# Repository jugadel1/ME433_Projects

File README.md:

# ME433

## HW2 - Alternate LED blinks using PIC32MX170F256B

- initializes A4 as input, and B4 and B5 as output
- in the infinite loop, wait until a newline is received from the computer, print it back, and if the USER button is not pressed, blink the LEDs 5 times over 2.5 seconds
- Edit the code to receive two numbers from the user over the serial port, the number of times to blink and how long each blink period should be.

## HW3 - Plot to terminal using UART using PIC32MX170F256B

- Every time you push the USER button, sends a single cycle of a sine wave in 100 data points to UART, with a 0.01 second delay between each data point.

- Uses sin_plotter.py to view the data as a graph.

## HW6 - Communicate with GPIO port extender using I2C

- The goal is to read from the button connected to GP0, and if pushed, turns on an LED connected to GP7, else turns off LED

## HW 14 - RC Motor Control

- Use the PIC to sweep the angle of the RC servo from 45 degrees to 135 degrees every 4 seconds

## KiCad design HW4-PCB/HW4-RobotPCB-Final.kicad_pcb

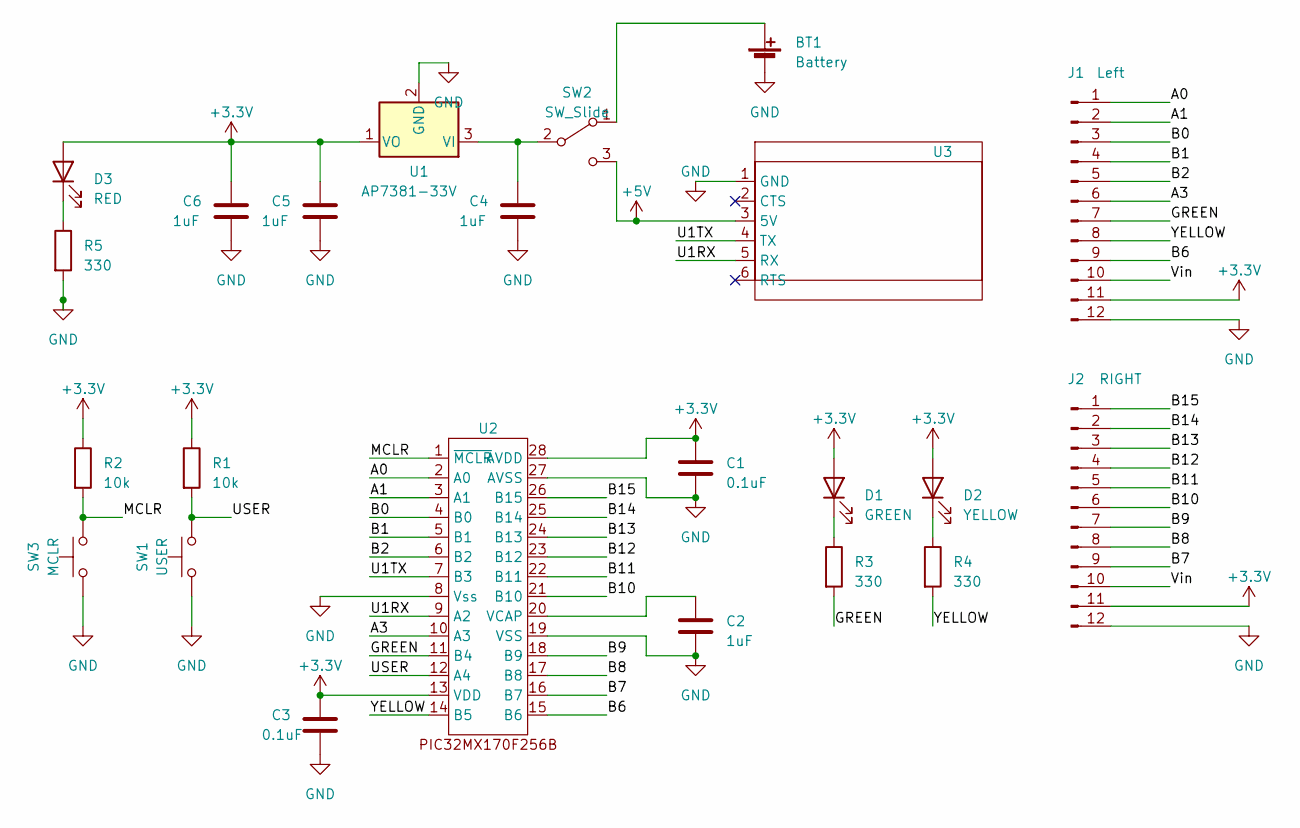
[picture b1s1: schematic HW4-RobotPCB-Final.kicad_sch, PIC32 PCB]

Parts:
BT1: Battery; PinSocket_1x02_P2.54mm_Vertical
C1, C3: 0.1uF; C_Disc_D3.4mm_W2.1mm_P2.50mm
C2: 1uF; C_Disc_D3.4mm_W2.1mm_P2.50mm
C4, C5, C6: 1uF; C_Disc_D5.1mm_W3.2mm_P5.00mm
D1: GREEN; LED_D3.0mm
D2: YELLOW; LED_D3.0mm
D3: RED; LED_D3.0mm
J1: Left; PinSocket_1x12_P2.54mm_Vertical
J2: RIGHT; PinSocket_1x12_P2.54mm_Vertical
R1, R2: 10k; R_Axial_DIN0207_L6.3mm_D2.5mm_P7.62mm_Horizontal
R3, R4, R5: 330; R_Axial_DIN0207_L6.3mm_D2.5mm_P7.62mm_Horizontal
SW1: USER; PinSocket_1x03_P2.54mm_Vertical
SW2: SW_Slide; Slide_ba-usb
SW3: MCLR; PinSocket_1x03_P2.54mm_Vertical
U1: AP7381-33V; TO-92L_Inline
U2: DIP-28_W7.62mm_Socket
U3: PinSocket_1x06_P2.54mm_Vertical

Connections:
+3.3V: C1.1, C3.1, C5.1, C6.1, D1.2 (A), D2.2 (A), D3.2 (A), J1.11, J2.11, R1.1, R2.1, U1.1 (VO), U2.13 (VDD), U2.28 (AVDD)
+5V: SW2.3 (C), U3.3 (5V)
/A0: J1.1, U2.2 (A0)
/A1: J1.2, U2.3 (A1)
/A3: J1.6, U2.10 (A3)
/B0: J1.3, U2.4 (B0)
/B1: J1.4, U2.5 (B1)
/B2: J1.5, U2.6 (B2)
/B6: J1.9, U2.15 (B6)
/B7: J2.9, U2.16 (B7)
/B8: J2.8, U2.17 (B8)
/B9: J2.7, U2.18 (B9)
/B10: J2.6, U2.21 (B10)
/B11: J2.5, U2.22 (B11)
/B12: J2.4, U2.23 (B12)
/B13: J2.3, U2.24 (B13)
/B14: J2.2, U2.25 (B14)
/B15: J2.1, U2.26 (B15)
/GREEN: J1.7, R3.2, U2.11 (B4)
/MCLR: R2.2, SW3.2, U2.1 (~MCLR)
/U1RX: U2.9 (A2), U3.5 (RX)
/U1TX: U2.7 (B3), U3.4 (TX)
/USER: R1.2, SW1.2, U2.12 (A4)
/Vin: J1.10, J2.10
/YELLOW: J1.8, R4.2, U2.14 (B5)
GND: BT1.2 (-), C1.2, C2.2, C3.2, C4.2, C5.2, C6.2, J1.12, J2.12, R5.2, SW1.1, SW3.1, U1.2 (GND), U2.8 (Vss), U2.19 (VSS), U2.27 (AVSS), U3.1 (GND)
unnamed: BT1.1 (+), SW2.1 (A)
unnamed: D1.1 (K), R3.1
unnamed: D2.1 (K), R4.1
unnamed: D3.1 (K), R5.1
unnamed: C4.1, SW2.2 (B), U1.3 (VI)
unnamed: C2.1, U2.20 (VCAP)

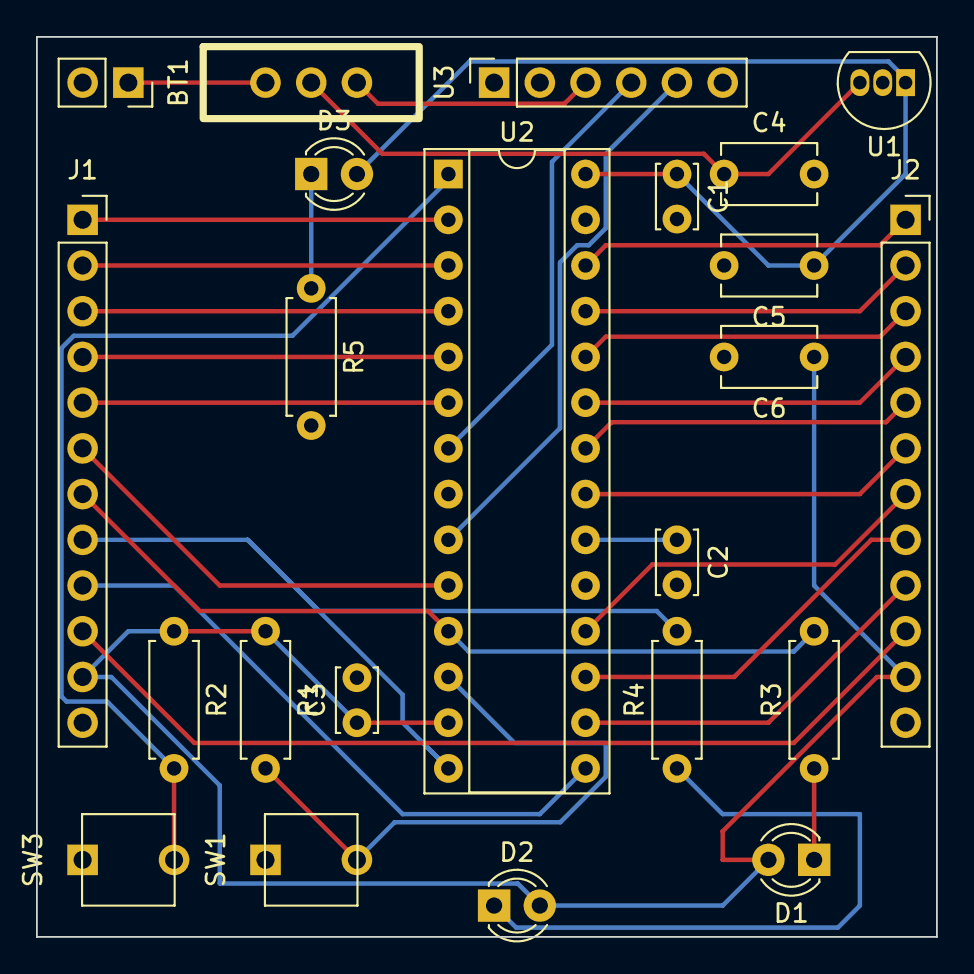
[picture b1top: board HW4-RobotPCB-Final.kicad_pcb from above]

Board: 2 copper layers, 50.0 x 50.0 mm, 23 parts (0 on the bottom side), 32 nets.

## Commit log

2023-04-19 "Finished HW3"
2023-04-19 "Finished
2023-04-19 "renamed"
2023-04-19 "edits"
2023-04-24 Finished SPI - Need to test
2023-04-25 fixed HW5
2023-04-25 start HW6
2023-04-28 started HW9
2023-05-02 finished HW6
2023-05-02 Setup neopixel code
2023-05-04 started hw7
2023-05-11 Finished IMU_reader
2023-05-11 Started OLED Project
2023-05-12 Finished DSP
2023-05-12 Finished OLED project
2023-05-17 started neopixel
2023-05-17 neopixel fixes
2023-05-17 neopixel fixes2
2023-05-18 fixed hw2
2023-05-18 reorganized hw2 folder
2023-05-24 Upload PCB Design
2023-05-26 fixed pico w http server, RC motor control
2023-05-26 uopdate eradme
2023-06-07 Started Final Project
2023-06-07 icontrol changes
2023-06-08 motot
